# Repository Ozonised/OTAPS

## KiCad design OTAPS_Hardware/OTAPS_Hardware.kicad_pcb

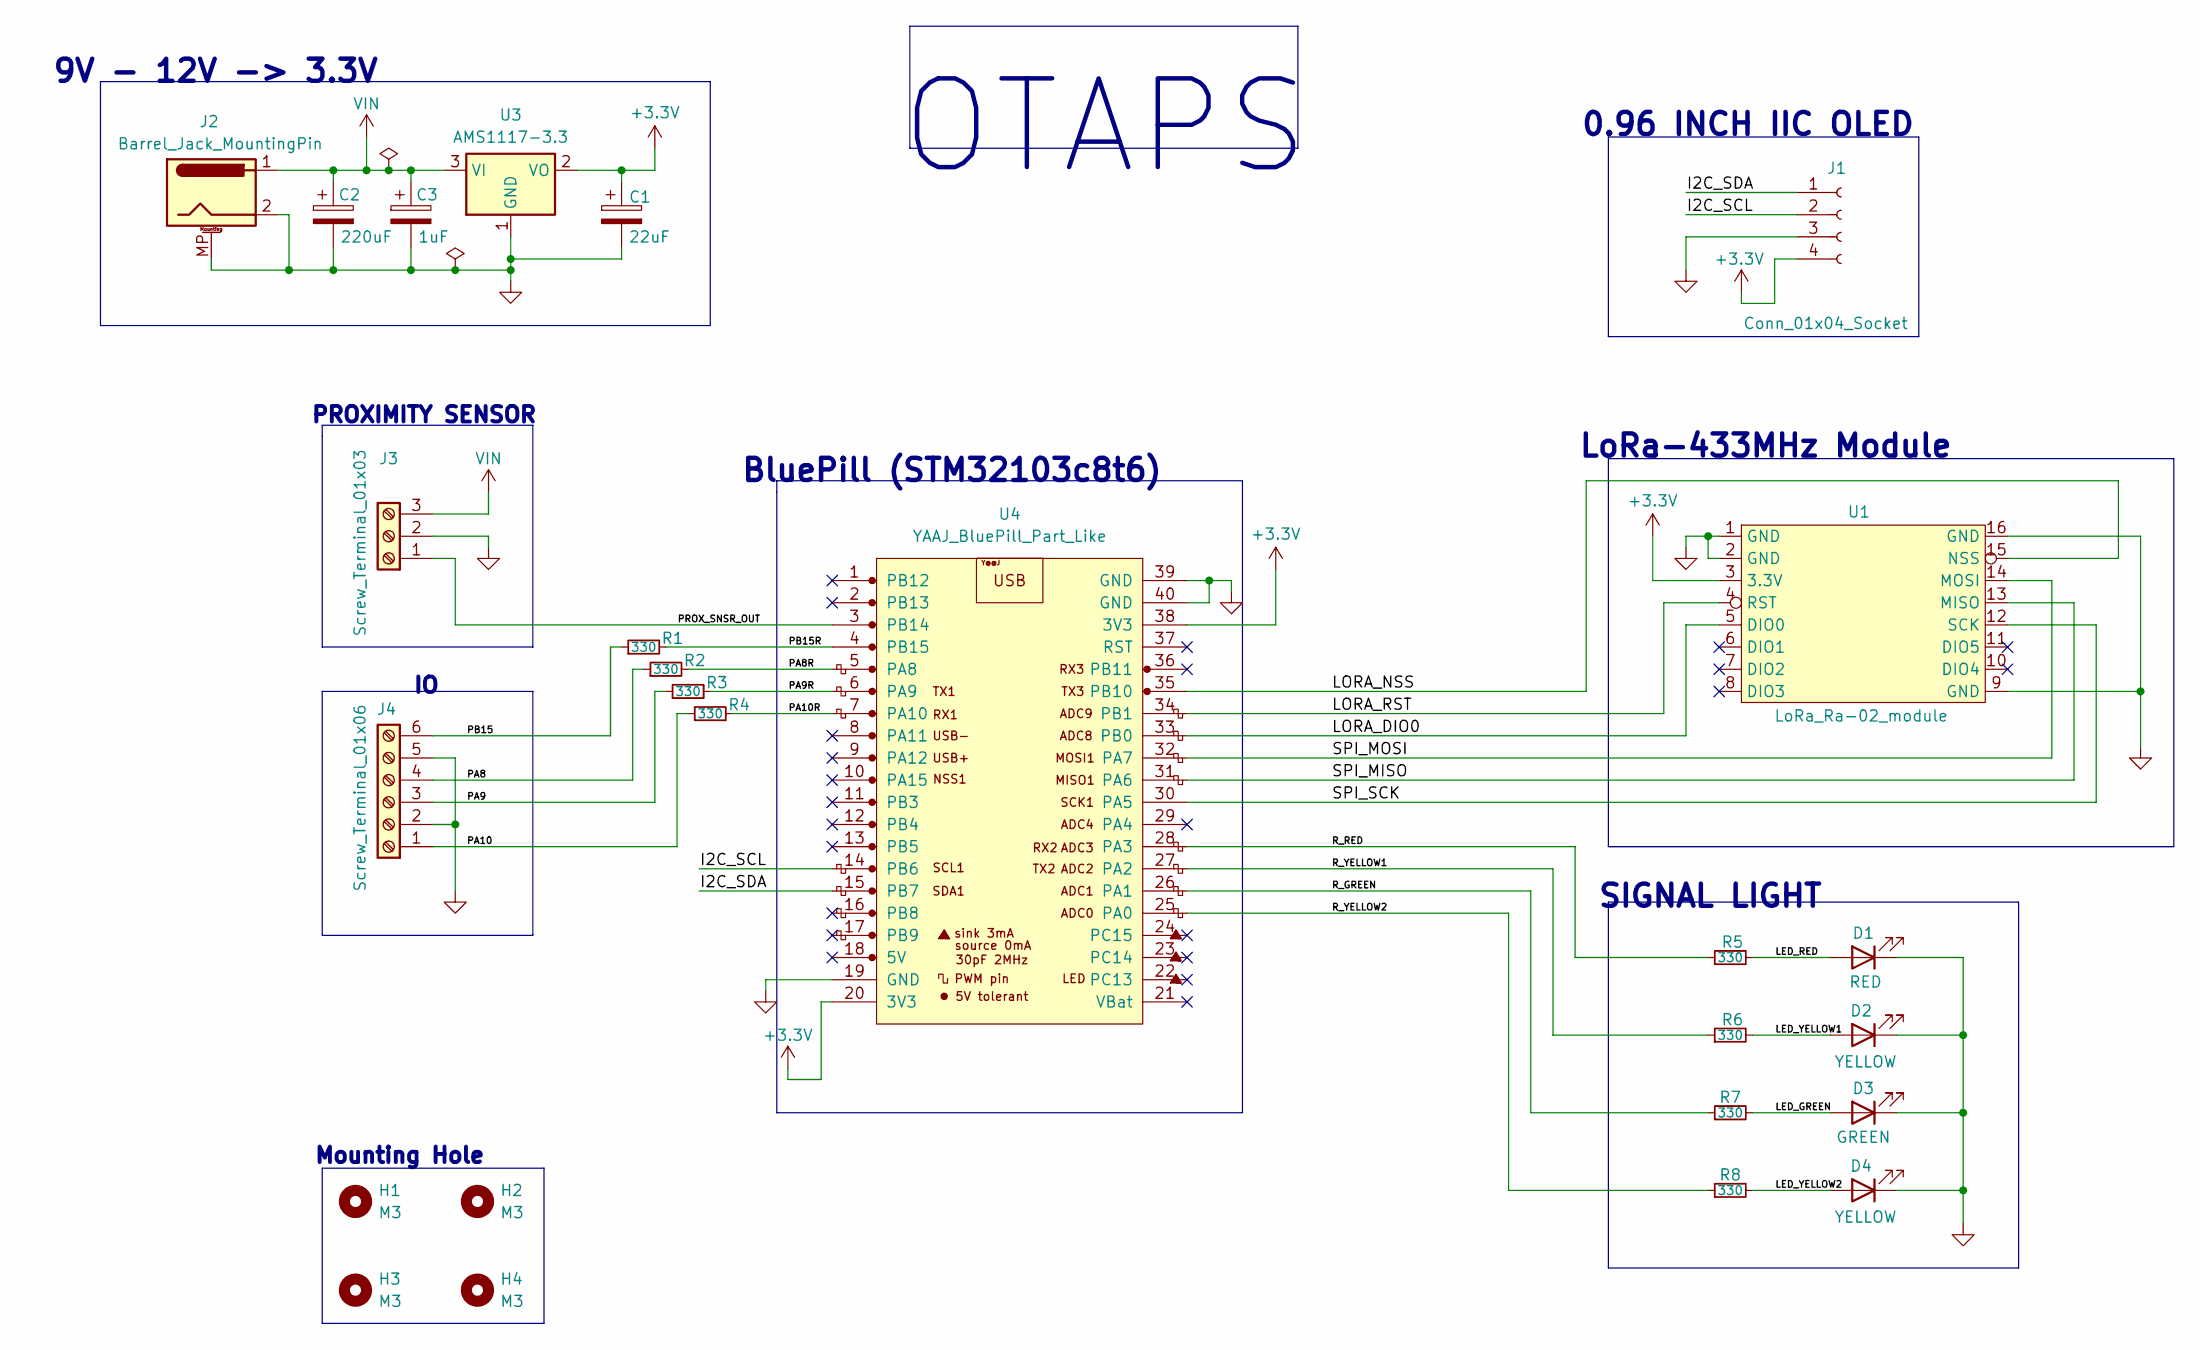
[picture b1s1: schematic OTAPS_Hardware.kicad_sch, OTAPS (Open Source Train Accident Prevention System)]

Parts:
C1: 22uF; CP_EIA-3528-15_AVX-H_Pad1.50x2.35mm_HandSolder
C2: 220uF; CP_Elec_8x10.5
C3: 1uF; C_1206_3216Metric_Pad1.33x1.80mm_HandSolder
D1: RED; LED_D3.0mm
D2, D4: YELLOW; LED_D3.0mm
D3: GREEN; LED_D3.0mm
H1, H2, H3, H4: M3; MountingHole_3.2mm_M3
J1: Conn_01x04_Socket; PinSocket_1x04_P2.54mm_Vertical
J2: Barrel_Jack_MountingPin; BarrelJack_Horizontal
J3: Screw_Terminal_01x03
J4: Screw_Terminal_01x06; TerminalBlock_Phoenix_MKDS-1,5-6_1x06_P5.00mm_Horizontal
R1, R2, R3, R4, R5, R6, R7, R8: 330; R_0603_1608Metric
U1: LoRa_Ra-02_module; DIP-16_988_ELL
U3: AMS1117-3.3; SOT-223-3_TabPin2
U4: YAAJ_BluePill_Part_Like; YAAJ_BluePill_1

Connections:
+3.3V: C1.1, J1.4, U1.3 (3.3V), U3.2 (VO), U4.20 (3V3), U4.38 (3V3)
/I2C_SCL: J1.2, U4.14 (PB6)
/I2C_SDA: J1.1, U4.15 (PB7)
/LED_GREEN: D3.2 (A), R7.2
/LED_RED: D1.2 (A), R5.2
/LED_YELLOW1: D2.2 (A), R6.2
/LED_YELLOW2: D4.2 (A), R8.2
/LORA_DIO0: U1.5 (DIO0), U4.33 (PB0)
/LORA_NSS: U1.15 (NSS), U4.35 (PB10)
/LORA_RST: U1.4 (RST), U4.34 (PB1)
/PA8: J4.4, R2.1
/PA8R: R2.2, U4.5 (PA8)
/PA9: J4.3, R3.1
/PA9R: R3.2, U4.6 (PA9)
/PA10: J4.1, R4.1
/PA10R: R4.2, U4.7 (PA10)
/PB15: J4.6, R1.1
/PB15R: R1.2, U4.4 (PB15)
/PROX_SNSR_OUT: J3.1, U4.3 (PB14)
/R_GREEN: R7.1, U4.26 (PA1)
/R_RED: R5.1, U4.28 (PA3)
/R_YELLOW1: R6.1, U4.27 (PA2)
/R_YELLOW2: R8.1, U4.25 (PA0)
/SPI_MISO: U1.13 (MISO), U4.31 (PA6)
/SPI_MOSI: U1.14 (MOSI), U4.32 (PA7)
/SPI_SCK: U1.12 (SCK), U4.30 (PA5)
GND: C1.2, C2.2, C3.2, D1.1 (K), D2.1 (K), D3.1 (K), D4.1 (K), J1.3, J2.2, J2.MP (MountPin), J3.2, J4.2, J4.5, U1.1 (GND), U1.2 (GND), U1.9 (GND), U1.16 (GND), U3.1 (GND), U4.19 (GND), U4.39 (GND), U4.40 (GND)
VIN: C2.1, C3.1, J2.1, J3.3, U3.3 (VI)

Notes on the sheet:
LoRa-433MHz Module
SIGNAL LIGHT
9V - 12V -> 3.3V
0.96 INCH IIC OLED
BluePill (STM32103c8t6)
OTAPS
Mounting Hole
PROXIMITY SENSOR

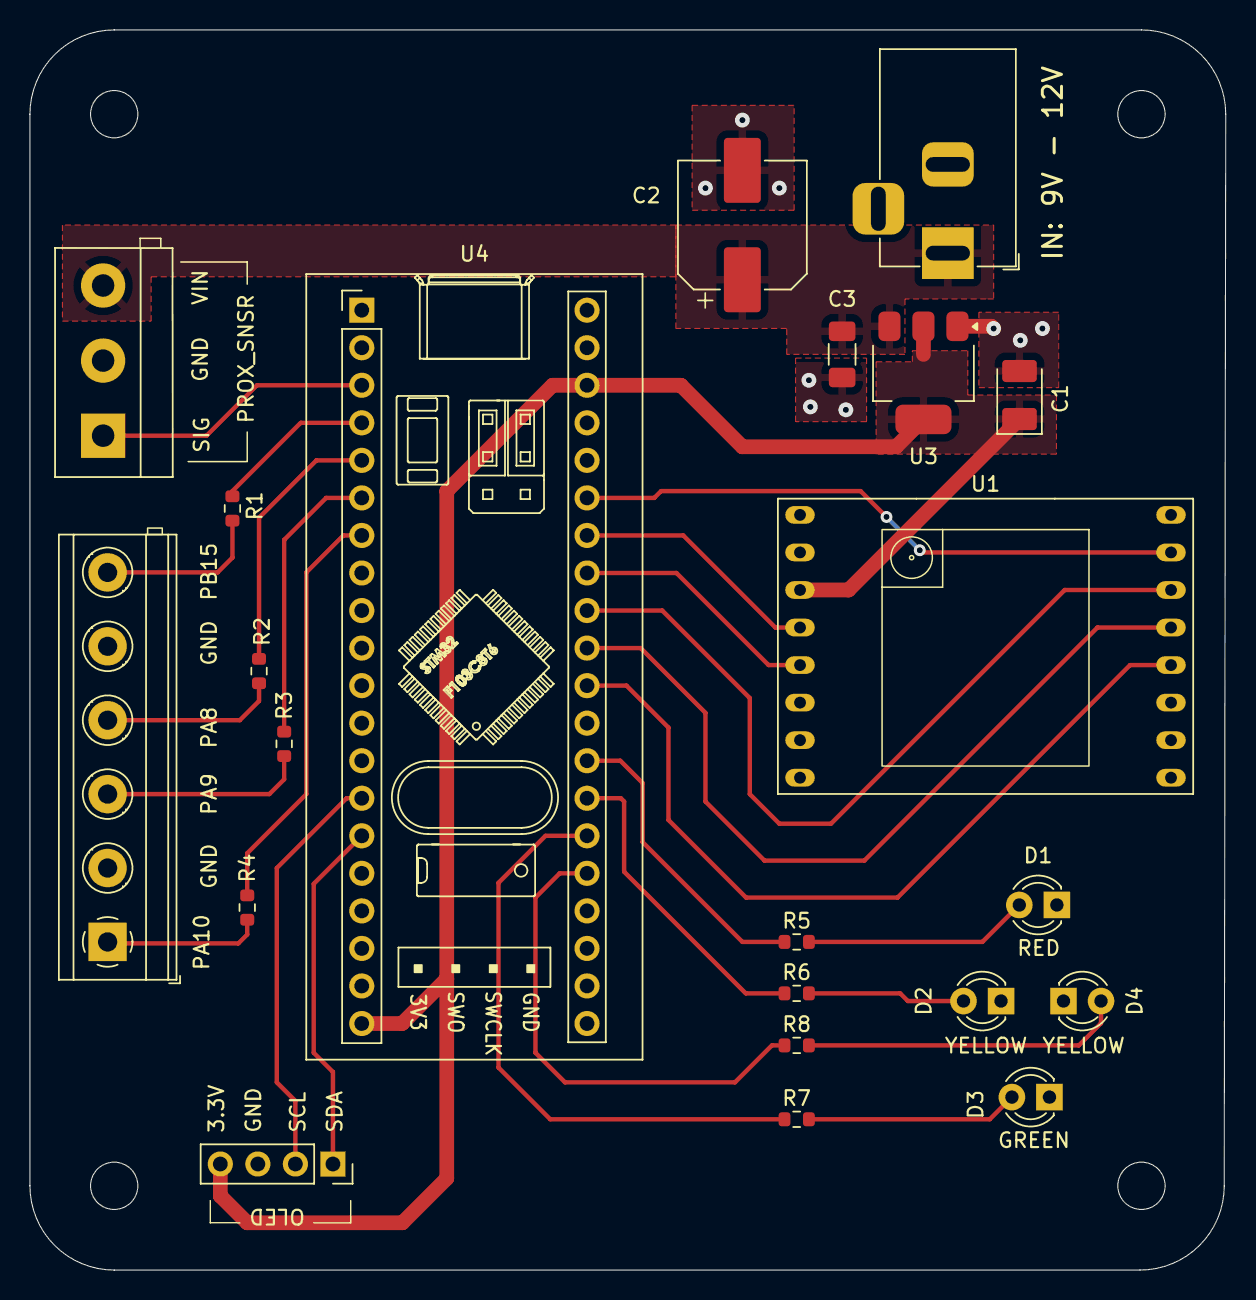
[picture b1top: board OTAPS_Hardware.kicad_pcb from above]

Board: 2 copper layers, 80.9 x 83.9 mm, 26 parts (0 on the bottom side), 28 nets.

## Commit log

2024-08-01 intial commit
2024-08-05 updated isNodeReady() and extracPayloadData
    fixed issue with isNodeReady() where it reset signalData[] in nextNode and prevNode
2024-08-05 changed communication protocol
    nodes now use different SF and BW instead of frequency
2024-08-05 added node() and nodeInit()
    removed postInit() & nodeInitialisation(), fixed issue with signal switching

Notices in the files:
OTAPS_Hardware/OTAPS_Hardware.kicad_pcb:
License: GNU General Public License version 3
